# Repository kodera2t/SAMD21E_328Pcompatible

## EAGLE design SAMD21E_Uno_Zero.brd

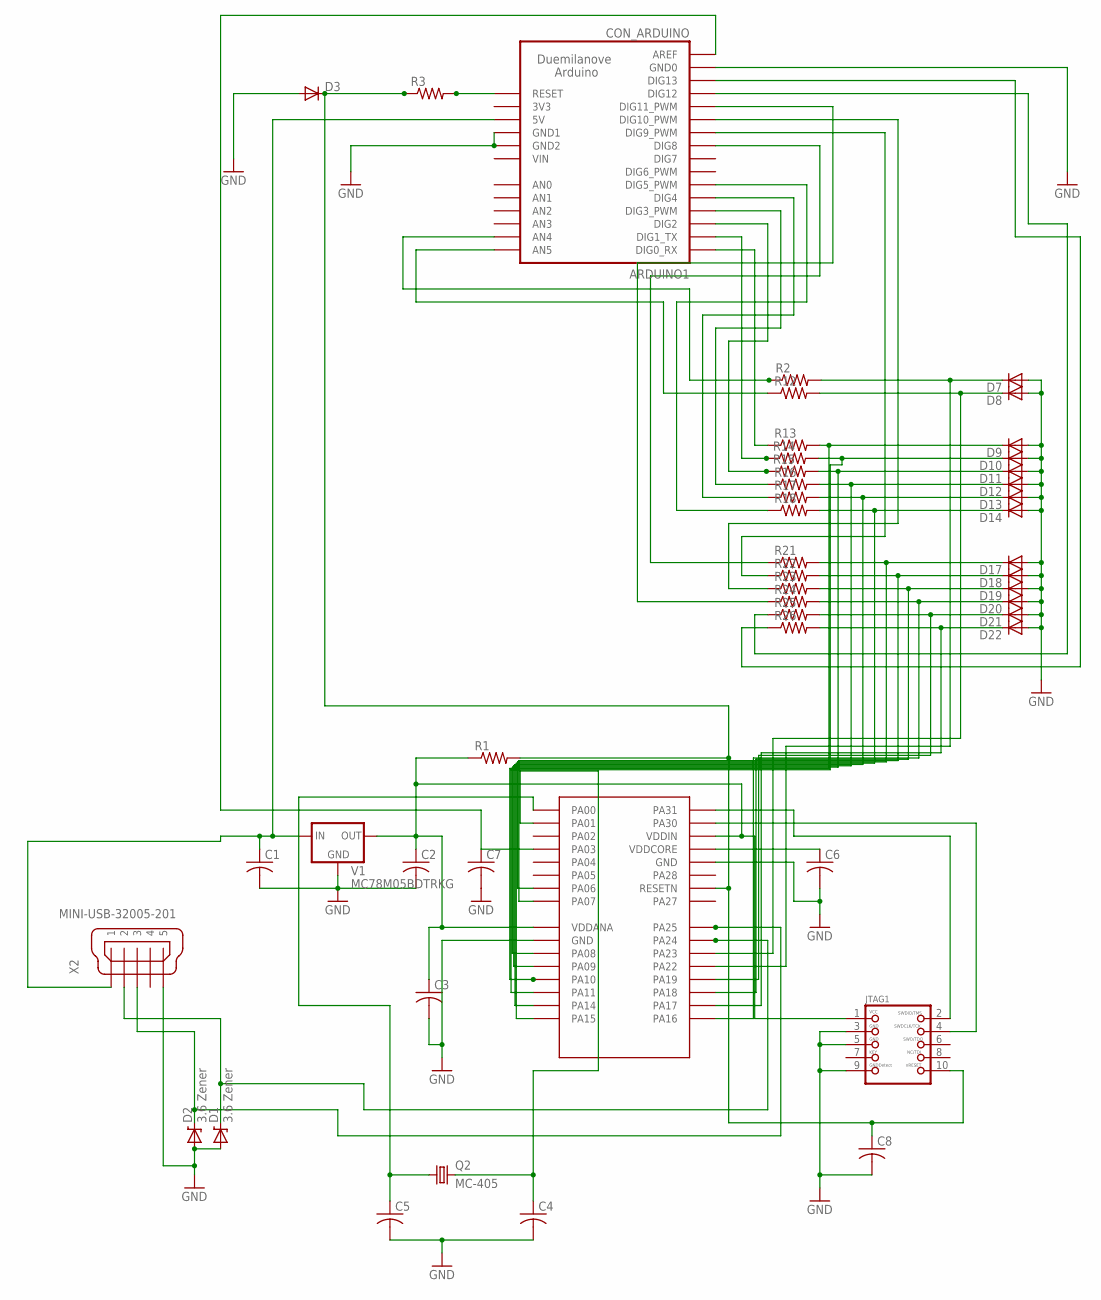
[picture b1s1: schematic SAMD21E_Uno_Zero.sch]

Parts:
ARDUINO1: CON_ARDUINO
C1, C2, C4, C5, C6, C7, C8: C-USC0603K; C0603K
C3: C-USC0603; C0603
D1, D2: 3.6 Zener; SOD-323
D3, D7, D8, D9, D10, D11, D12, D13, D14, D17, D18, D19, D20, D21, D22: DIODE-SOD323-W; SOD323-W
JTAG1: JTAG-CORTEXM3; 2X05_1.27MM_SMT
Q2: MC-405
R1, R2, R3, R12, R13, R14, R15, R16, R17, R18, R21, R22, R23, R24, R25, R26: R-US_R0603; R0603
U$8: ATSAMD21E18A-AU; 32-TQFP
V1: MC78M05BDTRKG; DPACK
X2: MINI-USB-32005-201; 32005-201

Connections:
GND: ARDUINO1.GND0, ARDUINO1.GND1, ARDUINO1.GND2, C1.2, C2.2, C3.2, C4.2, C5.2, C6.2, C7.2, C8.2, D1.2 (A), D2.2 (A), D3.A, D7.A, D8.A, D9.A, D10.A, D11.A, D12.A, D13.A, D14.A, D17.A, D18.A, D19.A, D20.A, D21.A, D22.A, JTAG1.3, JTAG1.5, JTAG1.9, U$8.10 (GND), U$8.28 (GND), V1.4 (GND), X2.5
unnamed: C2.1, C3.1, JTAG1.1, R1.1, U$8.9 (VDDANA), U$8.30 (VDDIN), V1.3 (OUT)
unnamed: JTAG1.4, U$8.31 (PA30)
unnamed: C4.1, Q2.2, U$8.2 (PA01)
unnamed: JTAG1.2, U$8.32 (PA31)
unnamed: C5.1, Q2.1, U$8.1 (PA00)
unnamed: ARDUINO1.RESET, R3.2
unnamed: C8.1, D3.C, JTAG1.10, R1.2, R3.1, U$8.26 (RESETN)
unnamed: C6.1, U$8.29 (VDDCORE)
unnamed: D1.1 (C), U$8.23 (PA24), X2.2
unnamed: D2.1 (C), U$8.24 (PA25), X2.3
unnamed: ARDUINO1.AREF, C7.1, U$8.4 (PA03)
unnamed: ARDUINO1.A_4 (AN4), R2.1
unnamed: ARDUINO1.A_5 (AN5), R12.1
unnamed: ARDUINO1.D_0 (DIG0_RX), R13.1
unnamed: ARDUINO1.5V, C1.1, V1.1 (IN), X2.1
unnamed: ARDUINO1.D_1 (DIG1_TX), R14.1
unnamed: ARDUINO1.D_2 (DIG2), R15.1
unnamed: ARDUINO1.D_3 (DIG3_PWM), R16.1
unnamed: ARDUINO1.D_4 (DIG4), R17.1
unnamed: ARDUINO1.D_5 (DIG5_PWM), R18.1
unnamed: ARDUINO1.D_8 (DIG8), R21.1
unnamed: ARDUINO1.D_9 (DIG9_PWM), R22.1
unnamed: ARDUINO1.D_10 (DIG10_PWM), R23.1
unnamed: ARDUINO1.D_11 (DIG11_PWM), R24.1
unnamed: ARDUINO1.D_12 (DIG12), R25.1
unnamed: ARDUINO1.D_13 (DIG13), R26.1
unnamed: D7.C, R2.2, U$8.21 (PA22)
unnamed: D8.C, R12.2, U$8.22 (PA23)
unnamed: D9.C, R13.2, U$8.13 (PA10)
unnamed: D10.C, R14.2, U$8.14 (PA11)
unnamed: D11.C, R15.2, U$8.11 (PA08)
unnamed: D12.C, R16.2, U$8.12 (PA09)
unnamed: D13.C, R17.2, U$8.15 (PA14)
unnamed: D14.C, R18.2, U$8.16 (PA15)
unnamed: D17.C, R21.2, U$8.7 (PA06)
unnamed: D18.C, R22.2, U$8.8 (PA07)
unnamed: D19.C, R23.2, U$8.19 (PA18)
unnamed: D20.C, R24.2, U$8.17 (PA16)
unnamed: D21.C, R25.2, U$8.20 (PA19)
unnamed: D22.C, R26.2, U$8.18 (PA17)
VIN: ARDUINO1.VIN

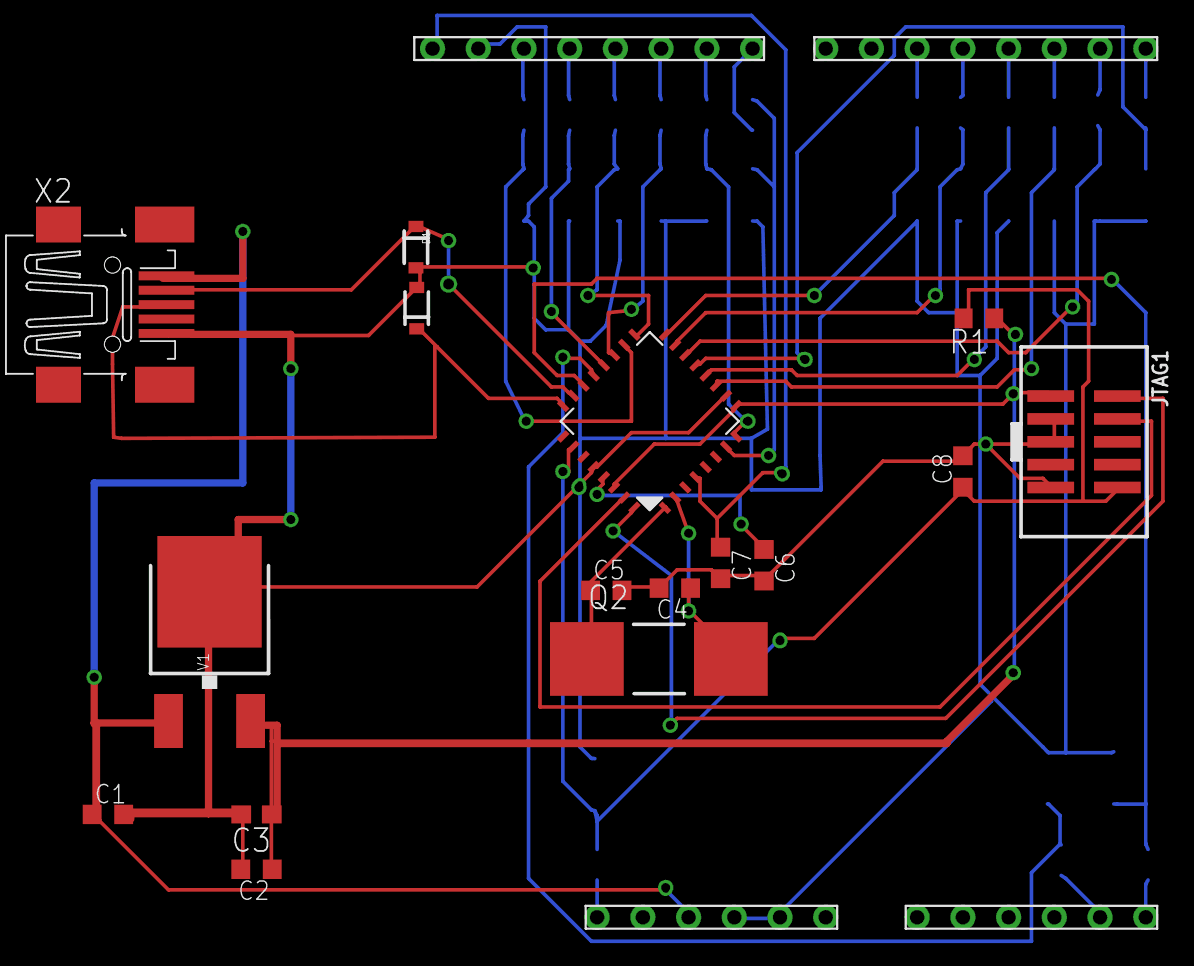
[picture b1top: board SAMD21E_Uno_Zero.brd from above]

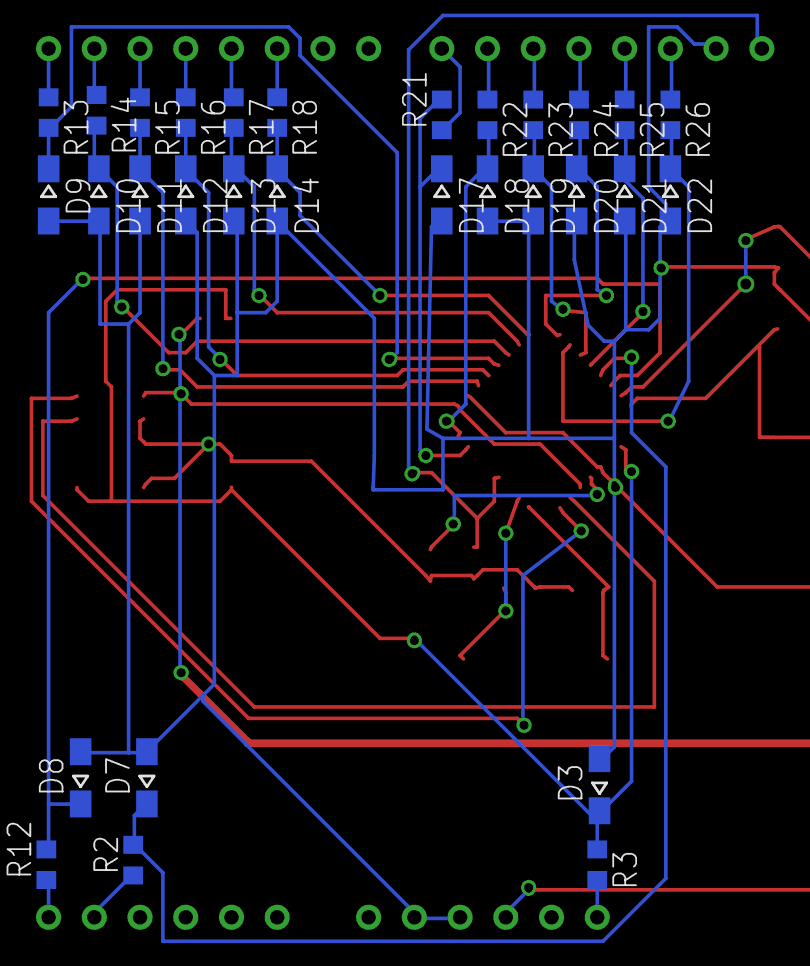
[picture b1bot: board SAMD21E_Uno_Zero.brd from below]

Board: 2 copper layers, 47 parts (30 on the bottom side), 41 nets.

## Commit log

2015-09-06 initial submission
2016-02-18 Uno_form_SAMD
2016-02-19 schematic

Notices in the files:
parts and their libraries:
SparkFun: Licensing: CC v3.0 Share-Alike You are welcome to use this library for commercial purposes.
OLED_mod: This work is placed in the public domain, and may be freely used for commercial and non-commercial work with the following conditions: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
